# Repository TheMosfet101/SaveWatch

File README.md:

# SaveWatch
A device used for the benefit of elderly people, which alert others and themselves whenever they fall or get too close towards an oncoming object. It uses Arduino Nano as the main board, a ADXL335 accelerometer,VL53L0X time of flight sensor,I2L LCD Adapter with an LCD display screen, and other passive/active components.

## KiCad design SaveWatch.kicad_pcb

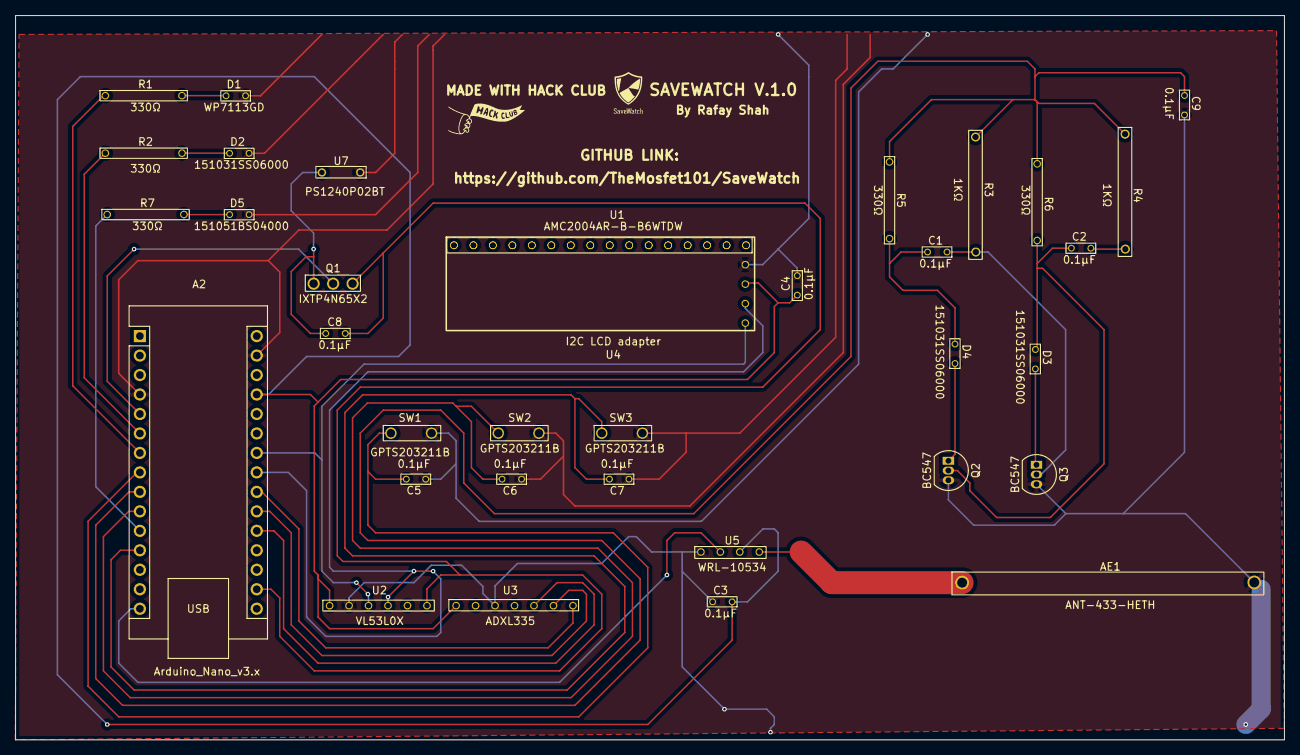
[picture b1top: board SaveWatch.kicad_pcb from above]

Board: 2 copper layers, 165.5 x 94.5 mm, 35 parts (0 on the bottom side), 27 nets.

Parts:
A2: Arduino_Nano_v3.x; Arduino_Nano
AE1: ANT-433-HETH; Antenna
C1, C2, C3, C4, C5, C6, C7, C8, C9: 0.1μF; 0.1μF Cap
D1: WP7113GD; Green LED
D2, D3, D4: 151031SS06000; Red LED
D5: 151051BS04000; Blue LED
Q1: IXTP4N65X2; MOSFET
Q2, Q3: BC547; TO-92_Inline
R1, R2, R5, R6, R7: 330Ω; 330Ω Resistor
R3, R4: 1KΩ; 1KΩ Resistor
SW1, SW2, SW3: GPTS203211B; Push Button
U1: AMC2004AR-B-B6WTDW; 20x4 LCD screen
U2: VL53L0X; VL53L0X TOF sensor
U3: ADXL335; ADXL335 3-Axis
U4: I2C LCD adapter; IC2 LCD adapter
U5: WRL-10534; RF Transmitter
U7: PS1240P02BT; Piezo Buzzer

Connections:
+3.3V: A2.17 (3V3), C8.1, Q1.3 (S), U2.6 (XSHUT)
+5V: A2.27 (+5V), C3.1, C4.2, U2.1 (VIN), U3.1 (VIN), U4.2 (VCC), U5.3 (VCC)
A1: A2.20 (A1), U3.5 (Z)
A2: A2.21 (A2), U3.6 (Y)
A3: A2.22 (A3), U3.7 (X)
A4: A2.23 (A4), U2.4 (SDA), U4.3 (SDA)
A5: A2.24 (A5), U2.3 (SCL), U4.4 (SCL)
D2: A2.5 (D2), Q1.2 (G)
D3: A2.6 (D3), R2.1
D4: A2.7 (D4), R1.1
D5: A2.8 (D5), C5.2, SW1.1
D6: A2.9 (D6), C9.2, R3.1, R4.1, R5.1, R6.1
D7: A2.10 (D7), C6.2, SW2.1
D8: A2.11 (D8), R7.1
D9: A2.12 (D9), C7.2, SW3.1
D12: A2.15 (D12), U5.2 (DATA)
GND: A2.4 (GND), A2.29 (GND), AE1.2, C3.2, C4.1, C5.1, C6.1, C7.1, C9.1, D1.1 (K), D2.1 (K), D5.1 (K), Q2.3 (E), Q3.3 (E), SW1.2, SW2.2, SW3.2, U2.2 (GND), U3.3 (GND), U4.1 (GND), U5.1 (GND), U7.1
unnamed: C2.1, R4.2
unnamed: D1.2 (A), R1.2
unnamed: D2.2 (A), R2.2
unnamed: C1.2, C2.2, D3.2 (A), D4.2 (A), Q2.2 (B), R5.2, R6.2
unnamed: D3.1 (K), Q3.1 (C)
unnamed: D4.1 (K), Q2.1 (C)
unnamed: D5.2 (A), R7.2
unnamed: C8.2, Q1.1 (D), U7.2
unnamed: C1.1, Q3.2 (B), R3.2
unnamed: AE1.1, U5.4 (ANT)

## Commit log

2026-04-05 Enhance README with images and clearer description
    Added images and improved description clarity.
2026-04-05 Update images in README
    Added a new image to the README and removed an old one.
2026-04-07 Create CODE
2026-04-10 Add new screenshots to README
    Added two new screenshots to the README for better visual representation.
2026-05-19 Refactor code for improved readability and functionality
